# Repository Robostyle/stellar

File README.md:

<picture>
    
</picture>

# Stellar split Keyboard

- Onshape model can be found [here](https://cad.onshape.com/documents/9f0ec04623bf66083821a7a0/w/c0bdf5da89aae74babc87fd1/e/22223dd23d8e8db672986c41)

# TODO

## PCB

- revision/made text is mirrored on `laR`.
- add silkscreen text for identifying the key, e.g. SW1, etc.
- set rotation on pinky to 10° instead to 5°.
- move the extra row next to the pinky column a bit up (next to the homerow?).

## Inspiration

- https://github.com/urob/zmk-config

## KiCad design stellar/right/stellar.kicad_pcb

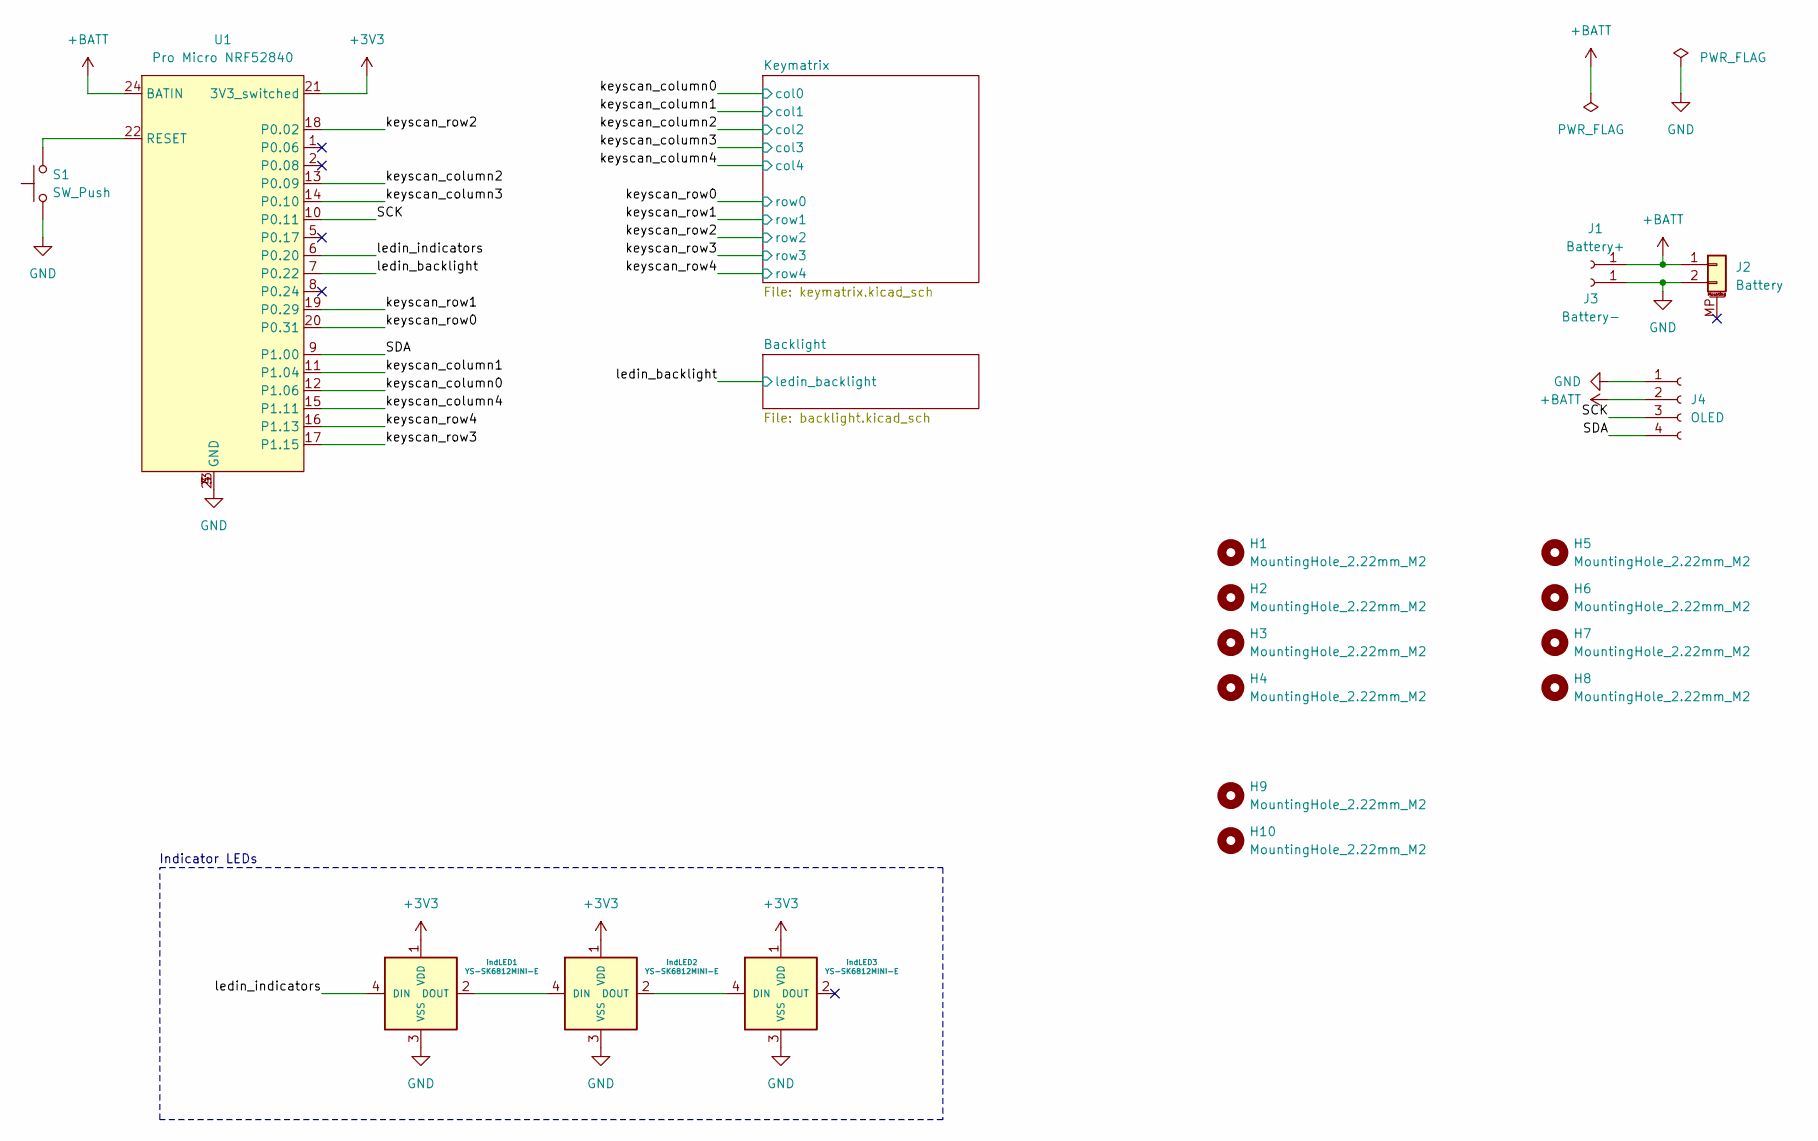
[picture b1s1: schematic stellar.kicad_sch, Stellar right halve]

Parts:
H1, H2, H3, H4, H9, H10: MountingHole_2.22mm_M2; MountingHole_2.2mm_M2_DIN965_Pad_TopOnly
H5, H6, H7, H8: MountingHole_2.22mm_M2; MountingHole_3.5mm
J1: Battery+; TestPoint_THTPad_D2.5mm_Drill1.2mm
J2: Battery; JST_PH_S2B-PH-SM4-TB_1x02-1MP_P2.00mm_Horizontal
J3: Battery-; TestPoint_THTPad_D2.5mm_Drill1.2mm
J4: OLED; JST_PH_S4B-PH-K_1x04_P2.00mm_Horizontal
S1: SW_Push; microswitch_3x4x2mm
U1: Pro Micro NRF52840; ProMicro-NoSilk
indLED1, indLED2, indLED3: YS-SK6812MINI-E

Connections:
+3V3: U1.21 (3V3_switched), indLED1.1 (VDD), indLED2.1 (VDD), indLED3.1 (VDD); also elsewhere on the board
+BATT: J1.1, J2.1, J4.2, U1.24 (BATIN)
/SCK: J4.3, U1.10 (P0.11)
/SDA: J4.4, U1.9 (P1.00)
/keyscan_column0: U1.12 (P1.06); also elsewhere on the board
/keyscan_column1: U1.11 (P1.04); also elsewhere on the board
/keyscan_column2: U1.13 (P0.09); also elsewhere on the board
/keyscan_column3: U1.14 (P0.10); also elsewhere on the board
/keyscan_column4: U1.15 (P1.11); also elsewhere on the board
/keyscan_row0: U1.20 (P0.31); also elsewhere on the board
/keyscan_row1: U1.19 (P0.29); also elsewhere on the board
/keyscan_row2: U1.18 (P0.02); also elsewhere on the board
/keyscan_row3: U1.17 (P1.15); also elsewhere on the board
/keyscan_row4: U1.16 (P1.13); also elsewhere on the board
/ledin_backlight: U1.7 (P0.22); also elsewhere on the board
/ledin_indicators: U1.6 (P0.20), indLED1.4 (DIN)
GND: J2.2, J3.1, J4.1, S1.1, U1.3 (GND), U1.4 (GND), U1.23 (GND), indLED1.3 (VSS), indLED2.3 (VSS), indLED3.3 (VSS); also elsewhere on the board
unnamed: S1.2, U1.22 (RESET)
unnamed: indLED1.2 (DOUT), indLED2.4 (DIN)
unnamed: indLED2.2 (DOUT), indLED3.4 (DIN)

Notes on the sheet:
Indicator LEDs

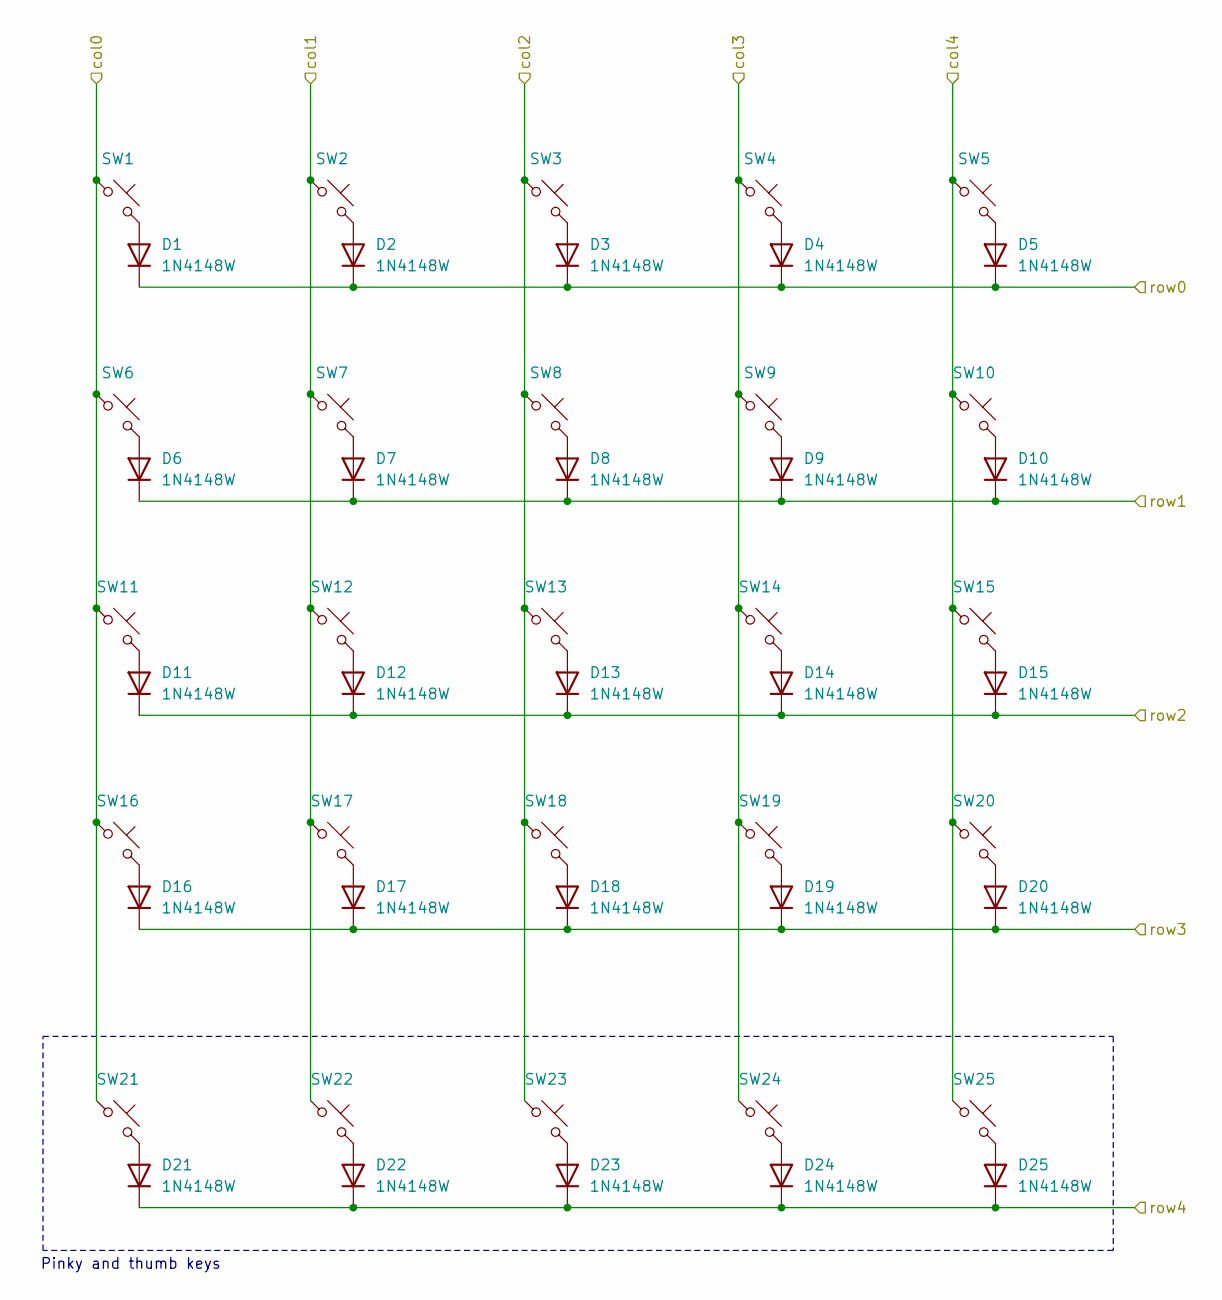
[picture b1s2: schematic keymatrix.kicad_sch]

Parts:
D1, D2, D3, D4, D5, D6, D7, D8, D9, D10, D11, D12, D13, D14, D15, D16, D17, D18, D19, D20, D21, D22, D23, D24, D25: 1N4148W; D_SOD-123
SW1, SW2, SW3, SW4, SW5, SW6, SW7, SW8, SW9, SW10, SW11, SW12, SW13, SW14, SW15, SW16, SW17, SW18, SW19, SW20, SW21, SW22, SW23, SW24, SW25: SW_Push_45deg; Kailh_socket_PG1350

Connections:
/keyscan_column0: SW1.1, SW6.1, SW11.1, SW16.1, SW21.1; also elsewhere on the board
/keyscan_column1: SW2.1, SW7.1, SW12.1, SW17.1, SW22.1; also elsewhere on the board
/keyscan_column2: SW3.1, SW8.1, SW13.1, SW18.1, SW23.1; also elsewhere on the board
/keyscan_column3: SW4.1, SW9.1, SW14.1, SW19.1, SW24.1; also elsewhere on the board
/keyscan_column4: SW5.1, SW10.1, SW15.1, SW20.1, SW25.1; also elsewhere on the board
/keyscan_row0: D1.1 (K), D2.1 (K), D3.1 (K), D4.1 (K), D5.1 (K); also elsewhere on the board
/keyscan_row1: D6.1 (K), D7.1 (K), D8.1 (K), D9.1 (K), D10.1 (K); also elsewhere on the board
/keyscan_row2: D11.1 (K), D12.1 (K), D13.1 (K), D14.1 (K), D15.1 (K); also elsewhere on the board
/keyscan_row3: D16.1 (K), D17.1 (K), D18.1 (K), D19.1 (K), D20.1 (K); also elsewhere on the board
/keyscan_row4: D21.1 (K), D22.1 (K), D23.1 (K), D24.1 (K), D25.1 (K); also elsewhere on the board
unnamed: D1.2 (A), SW1.2
unnamed: D2.2 (A), SW2.2
unnamed: D3.2 (A), SW3.2
unnamed: D4.2 (A), SW4.2
unnamed: D5.2 (A), SW5.2
unnamed: D6.2 (A), SW6.2
unnamed: D7.2 (A), SW7.2
unnamed: D8.2 (A), SW8.2
unnamed: D9.2 (A), SW9.2
unnamed: D10.2 (A), SW10.2
unnamed: D11.2 (A), SW11.2
unnamed: D12.2 (A), SW12.2
unnamed: D13.2 (A), SW13.2
unnamed: D14.2 (A), SW14.2
unnamed: D15.2 (A), SW15.2
unnamed: D16.2 (A), SW16.2
unnamed: D17.2 (A), SW17.2
unnamed: D18.2 (A), SW18.2
unnamed: D19.2 (A), SW19.2
unnamed: D20.2 (A), SW20.2
unnamed: D21.2 (A), SW21.2
unnamed: D22.2 (A), SW22.2
unnamed: D23.2 (A), SW23.2
unnamed: D24.2 (A), SW24.2
unnamed: D25.2 (A), SW25.2

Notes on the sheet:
Pinky and thumb keys

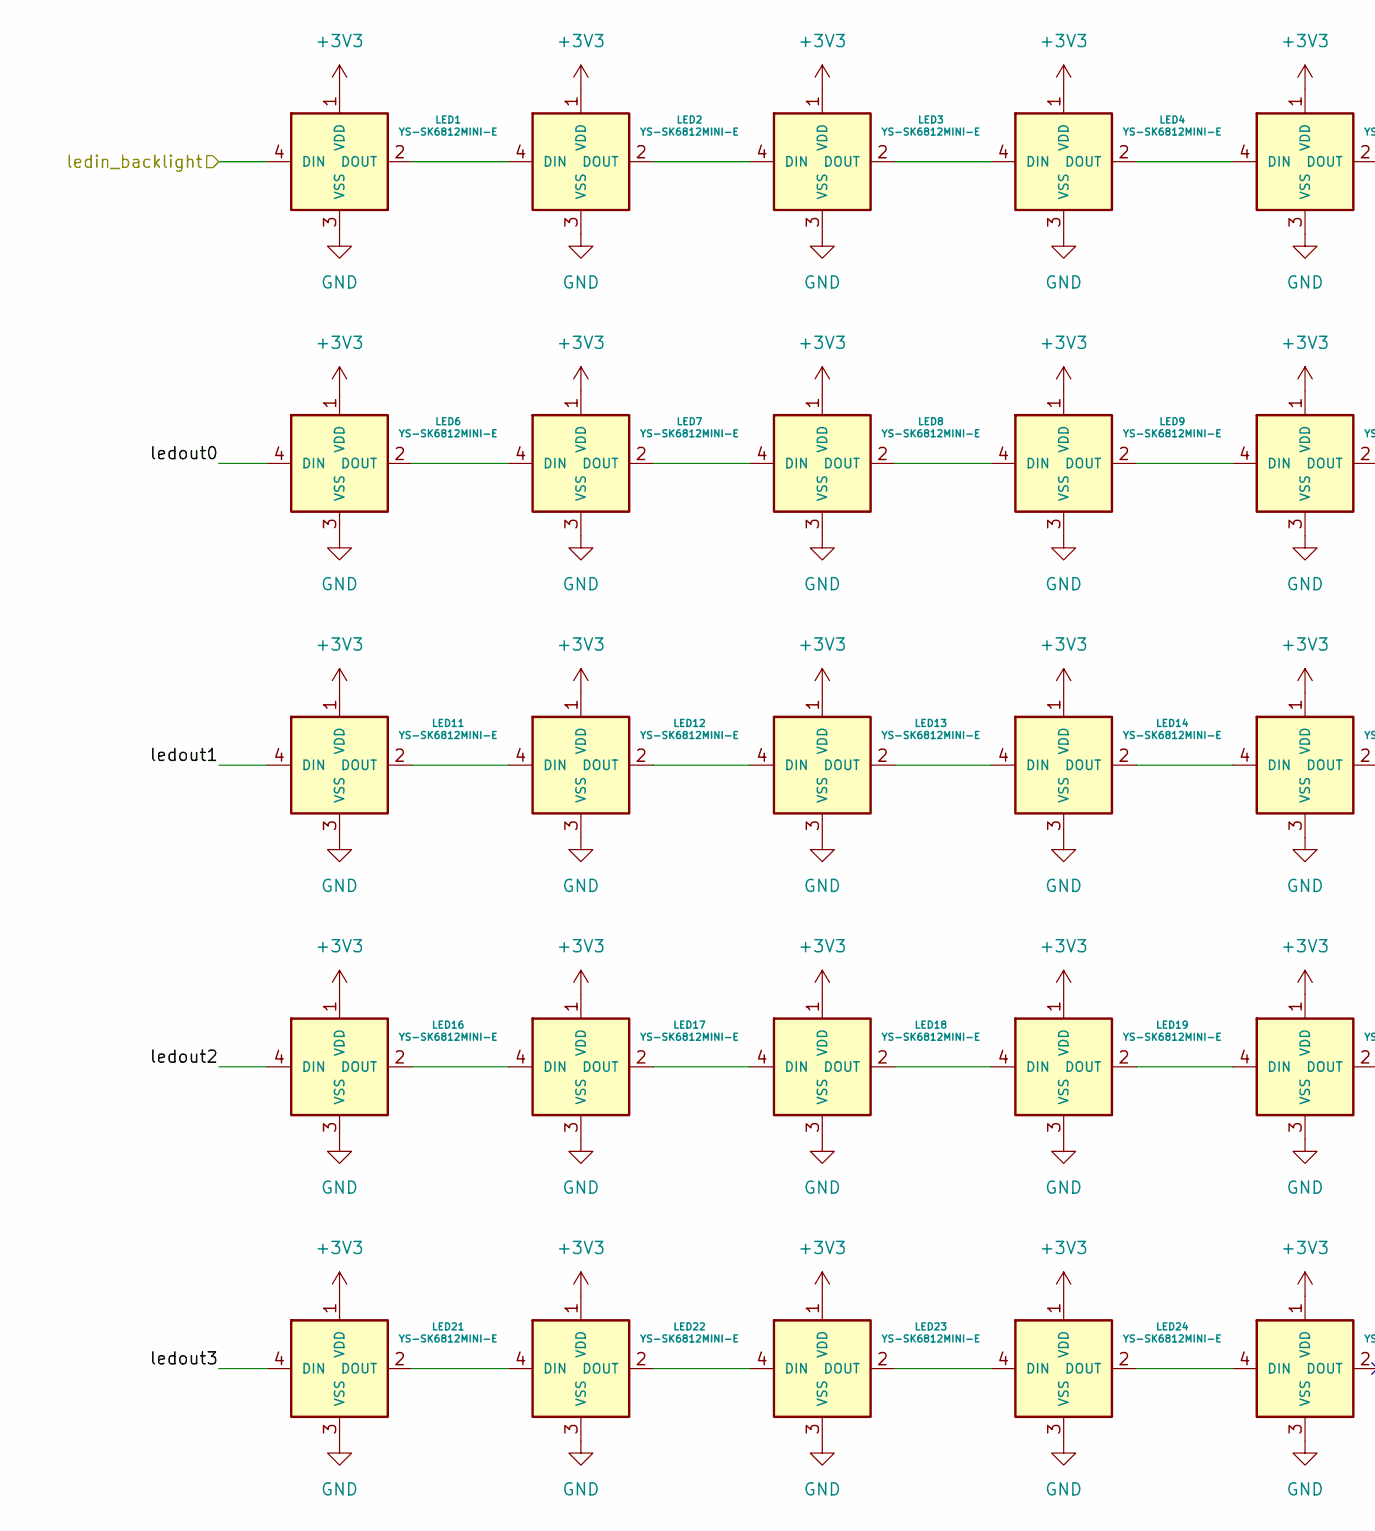
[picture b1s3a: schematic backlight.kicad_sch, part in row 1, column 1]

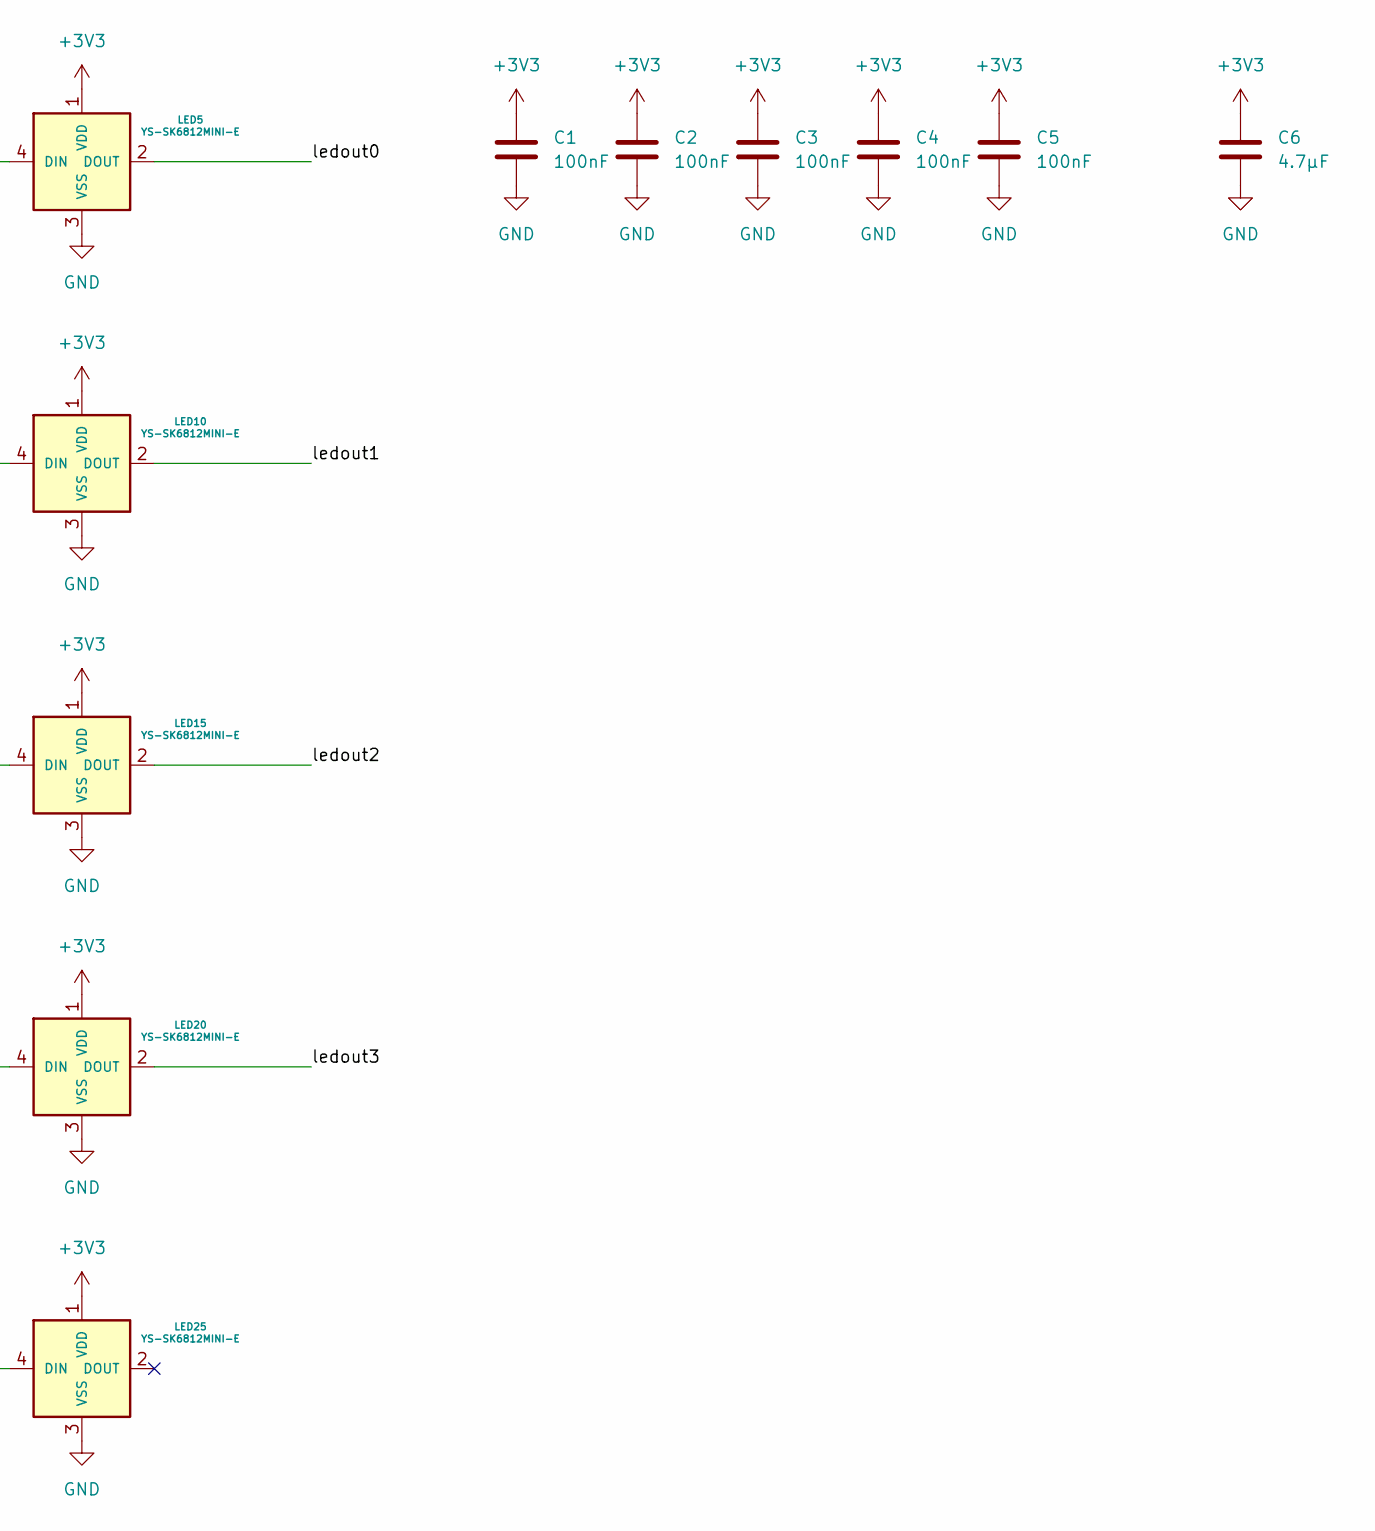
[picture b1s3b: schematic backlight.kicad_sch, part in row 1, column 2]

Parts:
C1, C2, C3, C4, C5: 100nF; C_0805_2012Metric
C6: 4.7μF; C_0805_2012Metric
LED1, LED2, LED3, LED4, LED5, LED6, LED7, LED8, LED9, LED10, LED11, LED12, LED13, LED14, LED15, LED16, LED17, LED18, LED19, LED20, LED21, LED22, LED23, LED24, LED25: YS-SK6812MINI-E

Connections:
+3V3: C1.1, C2.1, C3.1, C4.1, C5.1, C6.1, LED1.1 (VDD), LED2.1 (VDD), LED3.1 (VDD), LED4.1 (VDD), LED5.1 (VDD), LED6.1 (VDD), LED7.1 (VDD), LED8.1 (VDD), LED9.1 (VDD), LED10.1 (VDD), LED11.1 (VDD), LED12.1 (VDD), LED13.1 (VDD), LED14.1 (VDD), LED15.1 (VDD), LED16.1 (VDD), LED17.1 (VDD), LED18.1 (VDD), LED19.1 (VDD), LED20.1 (VDD), LED21.1 (VDD), LED22.1 (VDD), LED23.1 (VDD), LED24.1 (VDD), LED25.1 (VDD); also elsewhere on the board
/Backlight/ledout0: LED5.2 (DOUT), LED6.4 (DIN)
/Backlight/ledout1: LED10.2 (DOUT), LED11.4 (DIN)
/Backlight/ledout2: LED15.2 (DOUT), LED16.4 (DIN)
/Backlight/ledout3: LED20.2 (DOUT), LED21.4 (DIN)
/ledin_backlight: LED1.4 (DIN); also elsewhere on the board
GND: C1.2, C2.2, C3.2, C4.2, C5.2, C6.2, LED1.3 (VSS), LED2.3 (VSS), LED3.3 (VSS), LED4.3 (VSS), LED5.3 (VSS), LED6.3 (VSS), LED7.3 (VSS), LED8.3 (VSS), LED9.3 (VSS), LED10.3 (VSS), LED11.3 (VSS), LED12.3 (VSS), LED13.3 (VSS), LED14.3 (VSS), LED15.3 (VSS), LED16.3 (VSS), LED17.3 (VSS), LED18.3 (VSS), LED19.3 (VSS), LED20.3 (VSS), LED21.3 (VSS), LED22.3 (VSS), LED23.3 (VSS), LED24.3 (VSS), LED25.3 (VSS); also elsewhere on the board
unnamed: LED1.2 (DOUT), LED2.4 (DIN)
unnamed: LED2.2 (DOUT), LED3.4 (DIN)
unnamed: LED3.2 (DOUT), LED4.4 (DIN)
unnamed: LED4.2 (DOUT), LED5.4 (DIN)
unnamed: LED6.2 (DOUT), LED7.4 (DIN)
unnamed: LED7.2 (DOUT), LED8.4 (DIN)
unnamed: LED8.2 (DOUT), LED9.4 (DIN)
unnamed: LED9.2 (DOUT), LED10.4 (DIN)
unnamed: LED11.2 (DOUT), LED12.4 (DIN)
unnamed: LED12.2 (DOUT), LED13.4 (DIN)
unnamed: LED13.2 (DOUT), LED14.4 (DIN)
unnamed: LED14.2 (DOUT), LED15.4 (DIN)
unnamed: LED16.2 (DOUT), LED17.4 (DIN)
unnamed: LED17.2 (DOUT), LED18.4 (DIN)
unnamed: LED18.2 (DOUT), LED19.4 (DIN)
unnamed: LED19.2 (DOUT), LED20.4 (DIN)
unnamed: LED21.2 (DOUT), LED22.4 (DIN)
unnamed: LED22.2 (DOUT), LED23.4 (DIN)
unnamed: LED23.2 (DOUT), LED24.4 (DIN)
unnamed: LED24.2 (DOUT), LED25.4 (DIN)

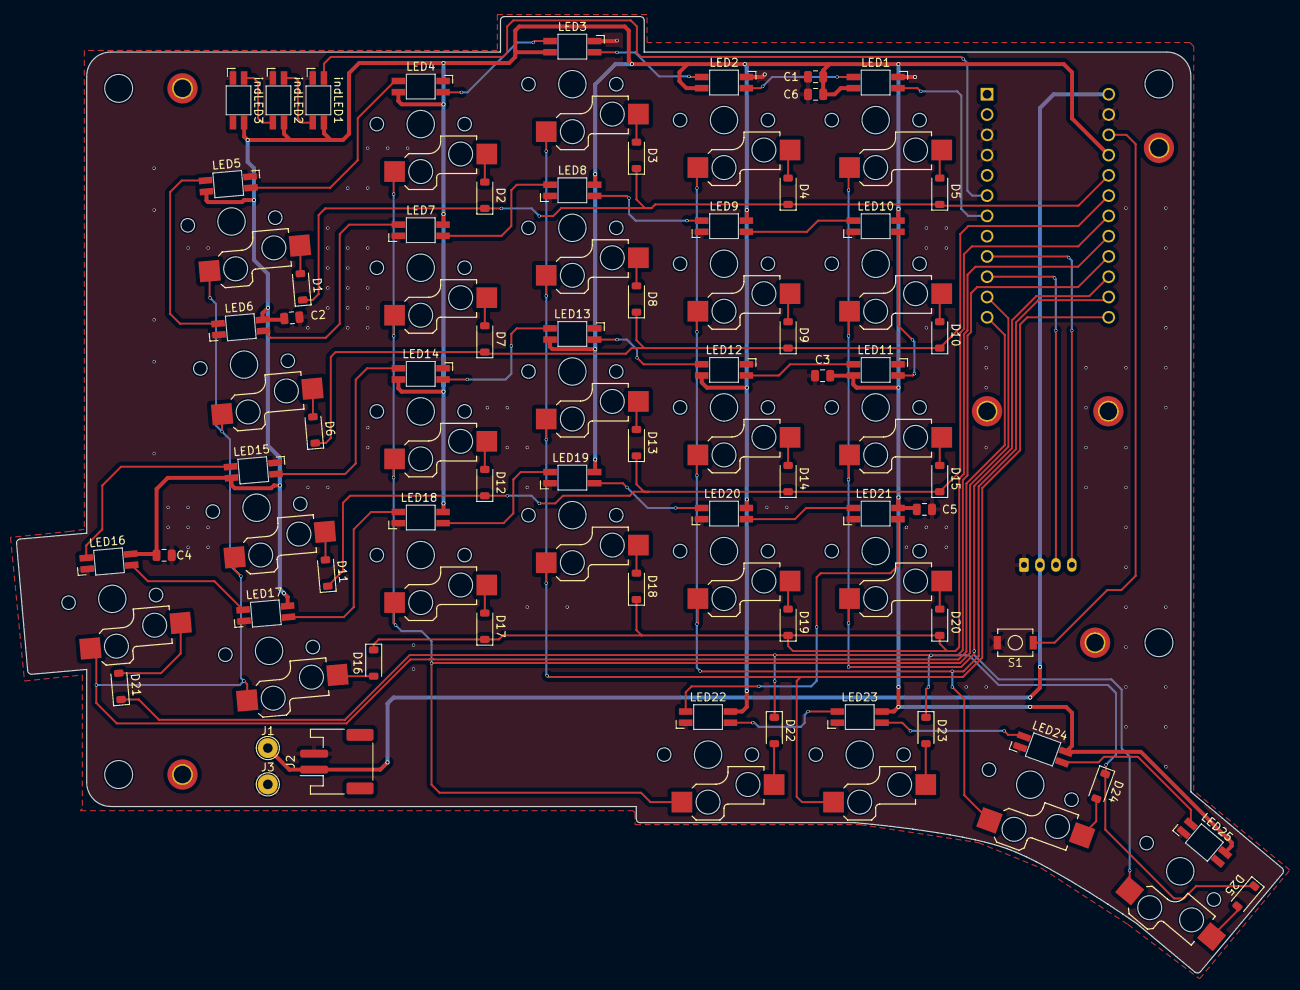
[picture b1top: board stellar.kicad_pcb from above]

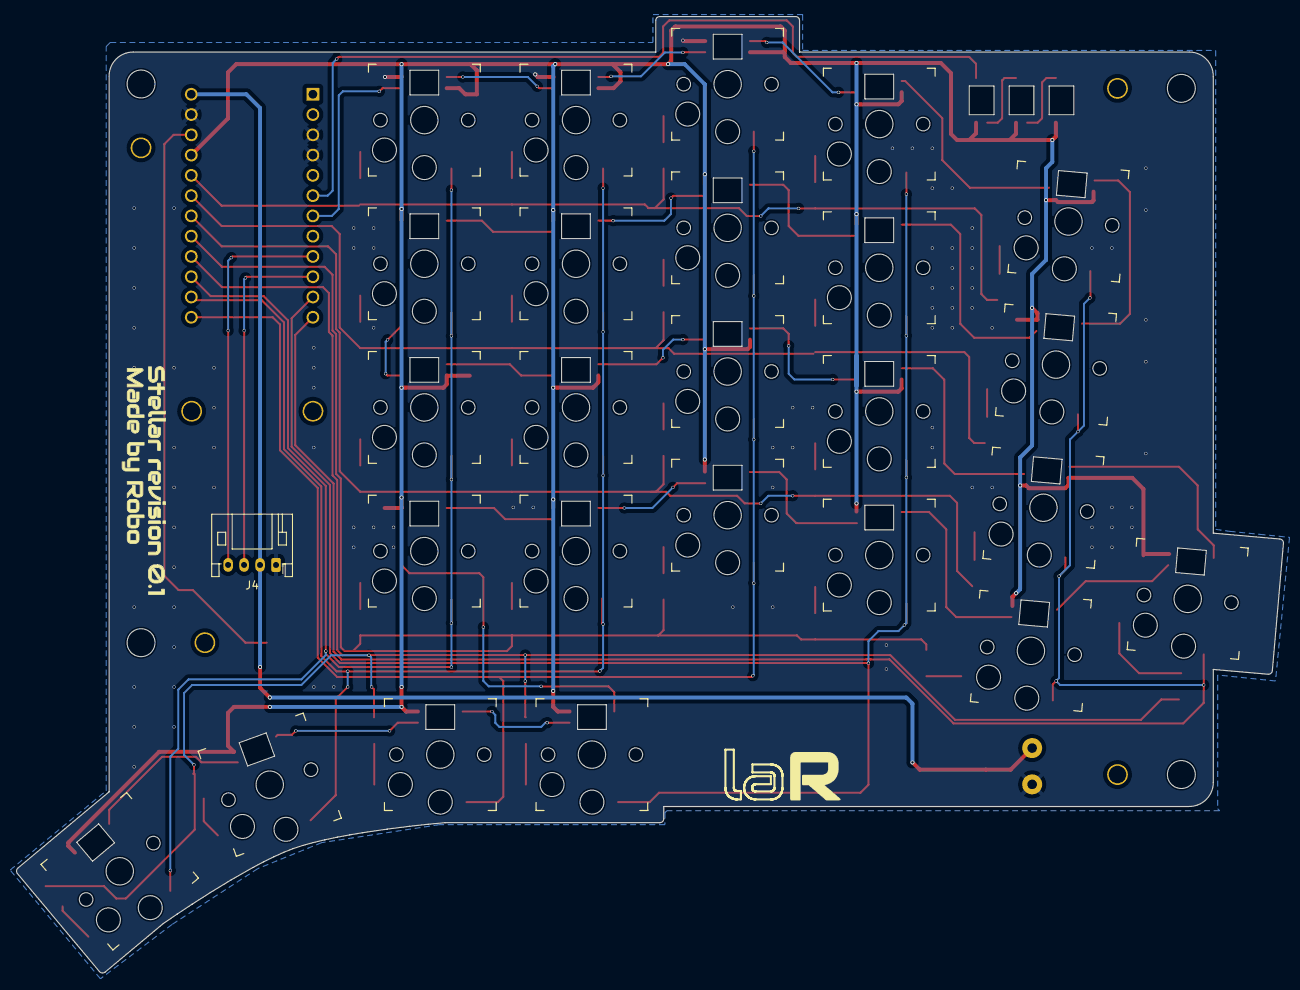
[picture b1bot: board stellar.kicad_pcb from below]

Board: 2 copper layers, 158.7 x 119.8 mm, 100 parts (28 on the bottom side), 69 nets.

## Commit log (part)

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2024-11-18 added left half
2024-11-18 [pcb] moved left halve to folder
2024-11-18 [pcb] removed backup file
2024-11-19 [pcb] moved to 'left' folder
2024-11-19 [pcb] initial right halve
2024-11-20 [pcb] right half layout done
2024-11-20 [pcb] right halve, more routing
2024-11-21 [pcb] final version, maybe
2024-11-21 [pcb] production files
2024-12-01 [pcb] fixed logo and added J1 con 3D model
2024-12-01 [pcb] moved to PCB folder
2024-12-04 [zmk] initial zmk configuration
2024-12-04 [doc] initial readme
2024-12-04 [doc] keyboard layout
2024-12-05 [keymap] initial (empty) layers
2024-12-07 [zmk] initial keymap
2024-12-08 [zmk] added symbols and nav
2024-12-10 [chore] added git ignore
2024-12-10 [doc] updated todo list
    Move these to tickets
2024-12-10 [doc] updated how to native build
2024-12-10 [zmk] updated keymap
2024-12-13 [pcb] updated paths to 3D models
2024-12-15 [case] added left and right case step files
2024-12-15 [zmk] changed symbols
2024-12-15 [zmk] added esc, ret, and tab to right halve
2024-12-19 [zmk] enable Bluetooth behaviors
2024-12-19 [zmk] tab combo on both halves
2024-12-31 [zmk] added media layer for RGB
2024-12-31 [zmk] removed unused things
2024-12-31 [zmk] changed right RSHFT to LSHFT
2024-12-31 [zmk] added print screen
2024-12-31 [zmk] added QWERTY layer for gaming
2025-01-01 [zmk] enabled RGB underglow
2025-01-01 [zmk] added TODO.md
2025-01-01 [zmk] some polishing
    Fixed game layer. Added more keys to the keypad and re-ordered the
    symbols. Added some system keys.
2025-01-02 [zmk] moved config go root
2025-01-16 wip indicator leds
2025-01-26 [zmk] moved key labels header file
2025-01-26 [keymap] initial keymap drawer config
    Added an initial config for the stellar keyboard and a config for keymap
    drawer. It is not perfect yet, but it works and gives a nice overview.
2025-01-26 [zmk] changed symbols layer
2025-01-26 [zmk] combos changed
    Removed enter, escape, and tab from other layers. Added tab to the
    gaming layer. Changed copy and paste combos. Removed the no longer used
    combo to switch off the gaming layer.
2025-01-26 [zmk] added sleep states
2025-01-26 [zmk] added soft off and toggle gaming layer
    This adds a soft off behavior to shutdown the key board. Added a toggle
    for the gaming layer. Also removed the stop for stopping playing media.
2025-01-26 [git] added git attributes for keymap/dtsi files
2025-01-26 [zmk] added numeric keys to homerow mods trigger pos
2025-01-26 [zmk] wrong order of num keys to trigger pos
2025-01-26 [case] added a reset button to bottom
2025-01-26 [case] added a keyboard holder/travel case
    Added a nice holder and/or travel case to hold the two halves. I will
    iterate over this a bit, since the top of the two halve will rub
    together when put in a back pack.
2025-01-26 [doc] added PCB images, traces, and schematic PDFs
2025-01-29 [zmk] removed soft off delay
2025-01-29 [zmk] reordered keys for more convenience
    The sys layer has is own key instead of pressing to. Fixed issues with
    the num layout. Moved bluetooth modifiers to media layer.
2025-02-05 [zmk] added .cache to .gitignore
2025-02-05 [zmk] changed and added some combos
    * esc and ret now only on left hand
    * moved tab to LM3 and LM2 and allow LALT when hold
    * added horizontal combos right hand for bspc and del
    * added vertical combos right hand for colon and semi
2025-02-11 [zmk] added brackets to vertical combos
2025-02-12 [zmk] some spacing
2025-02-12 [zmk] added more combos
    Changed some of the positions for the brackets and added some combos for
    often used symbols.
2025-02-13 [zmk] lots of changes to key layout
    * removed symbols from SYM layer in favor of vertical combos.
    * renamed SYM layer back to NUM layer.
    * moved bluetooth clear profile to right halve and added extra profile.
    * CANCEL to nav layer.
    * replaced question/fslh with sqt/dqt.
2025-02-14 [zmk] synced parts with urob's github repo
2025-02-25 [zmk] added workspace change and some other changes
    * Re-ordered thumb keys
    * Changed some navigation keys
    * Added keys to move through Hyprland workspaces [LGUI + <num>]
2025-02-25 [zmk] added simple Makefile for local building
2025-06-10 feat(zmk) improved gaming layer
    Added a full qwerty layout and a shifted layout. Most keys for gaming
    should be present now.
2025-09-30 feat(zmk) removed some combos and key layout changes
2025-09-30 feat(zmk) merged num and nav layer new sym layer
    This merges the numeric and navigation layers, allowing for a dedicated
    symbol layer. A future commit will remove the combos for the symbols, as
    I can't get used to it (too many misses resulting in double keystrokes).
2025-09-30 feat(zmk) removed all symbol combos
2025-10-01 feat(zmk) swapped some keys
2025-10-22 feat(zmk) swapped layer keys fixed qwerty
2025-12-12 feat(zmk) moved symbols around
    Symbols moved and layer keys changed
2026-05-03 feat (zmk) add reset firmware target
2026-05-03 feat (zmk) keymap tweaks
2026-05-03 feat (zmk) add github build action
2026-05-03 feat (zmk) add build config yaml
2026-05-03 feat (zmk) prepare for v0.4
2026-05-03 feat (ZMK) added bluetooth nxt/prv and out toggle
2026-05-11 feat (zmk) moved home/end/ins remove double del
2026-06-18 feat (zmk) reworked keymap
    Loads of things;
    * removed magic shift
    * bring back of combos for symbols
    * removed symbol layer
    * added word_cap with lshf + tap rshft
    * swapped enter, tab, space (painful)
